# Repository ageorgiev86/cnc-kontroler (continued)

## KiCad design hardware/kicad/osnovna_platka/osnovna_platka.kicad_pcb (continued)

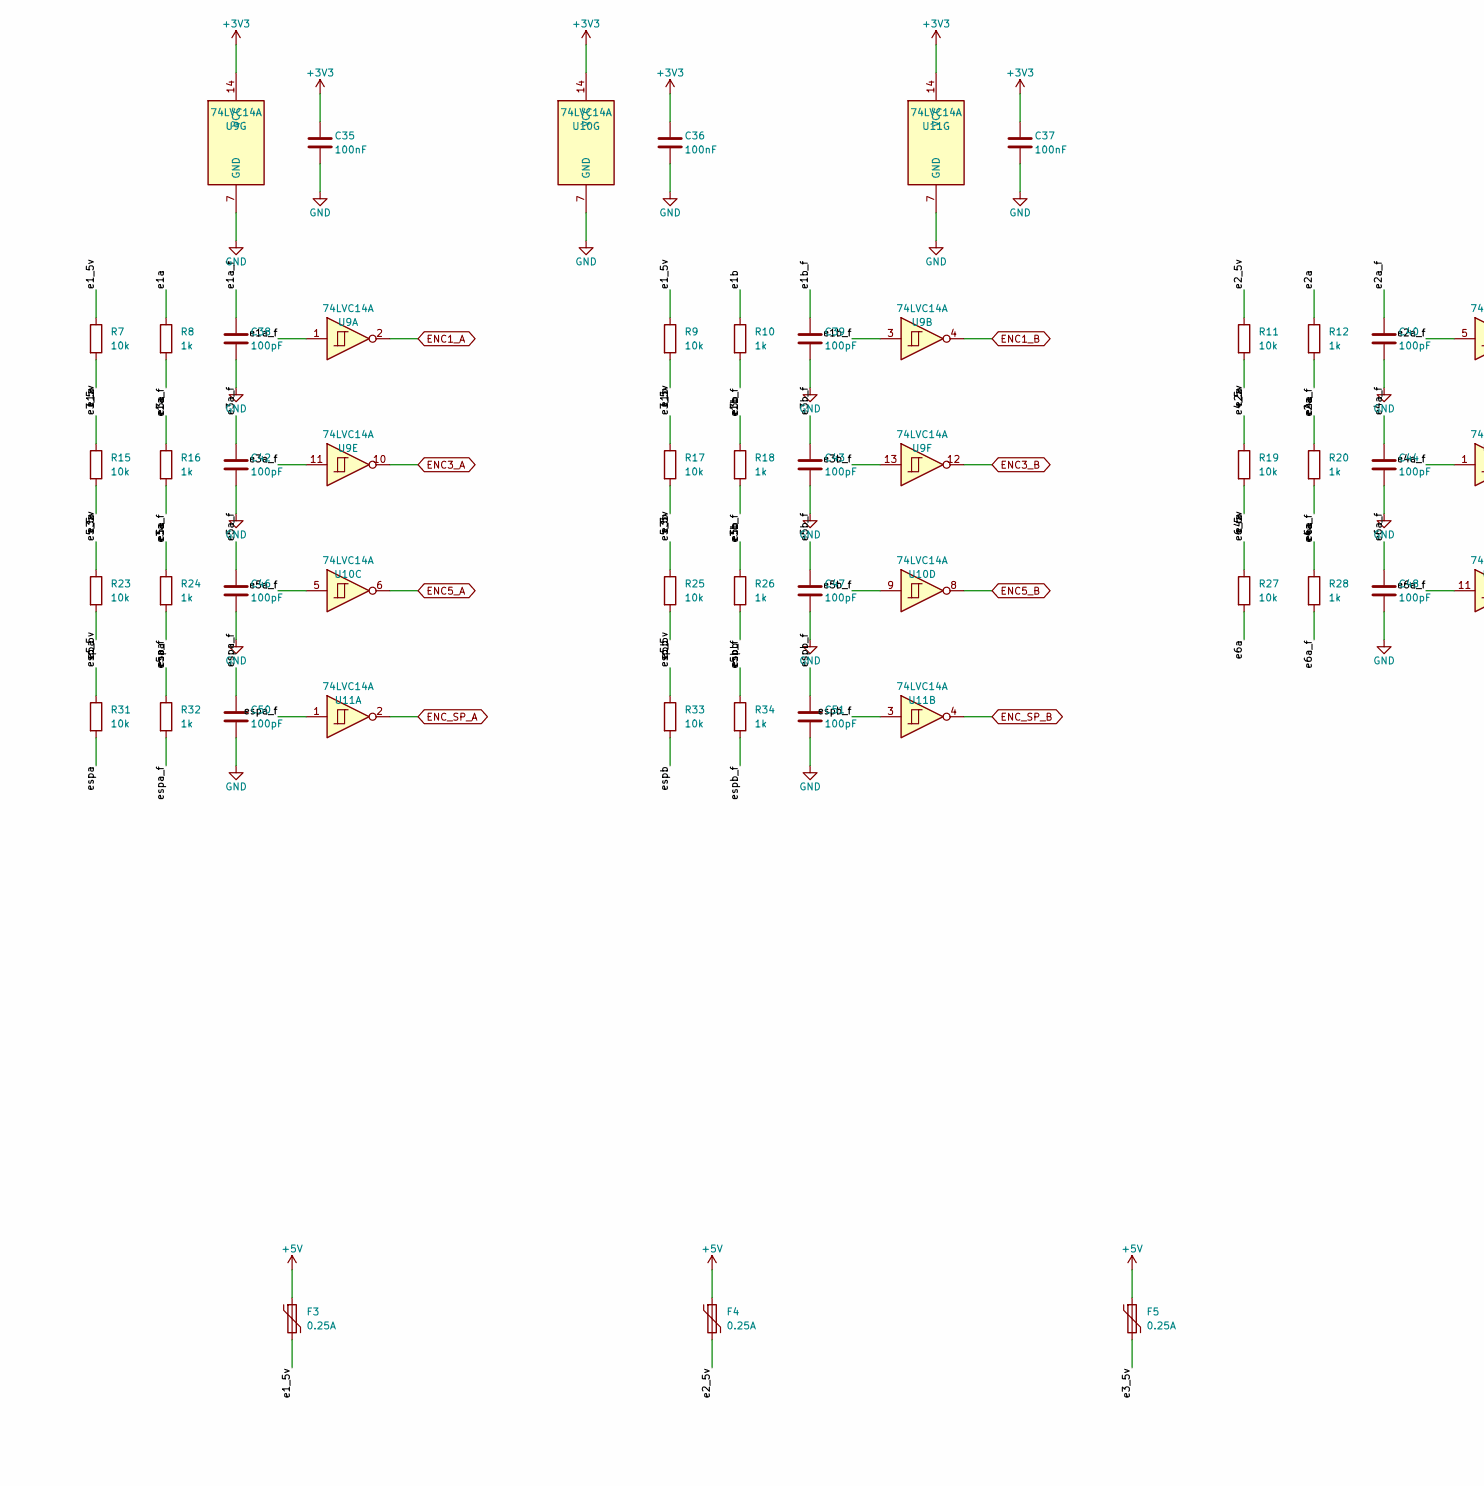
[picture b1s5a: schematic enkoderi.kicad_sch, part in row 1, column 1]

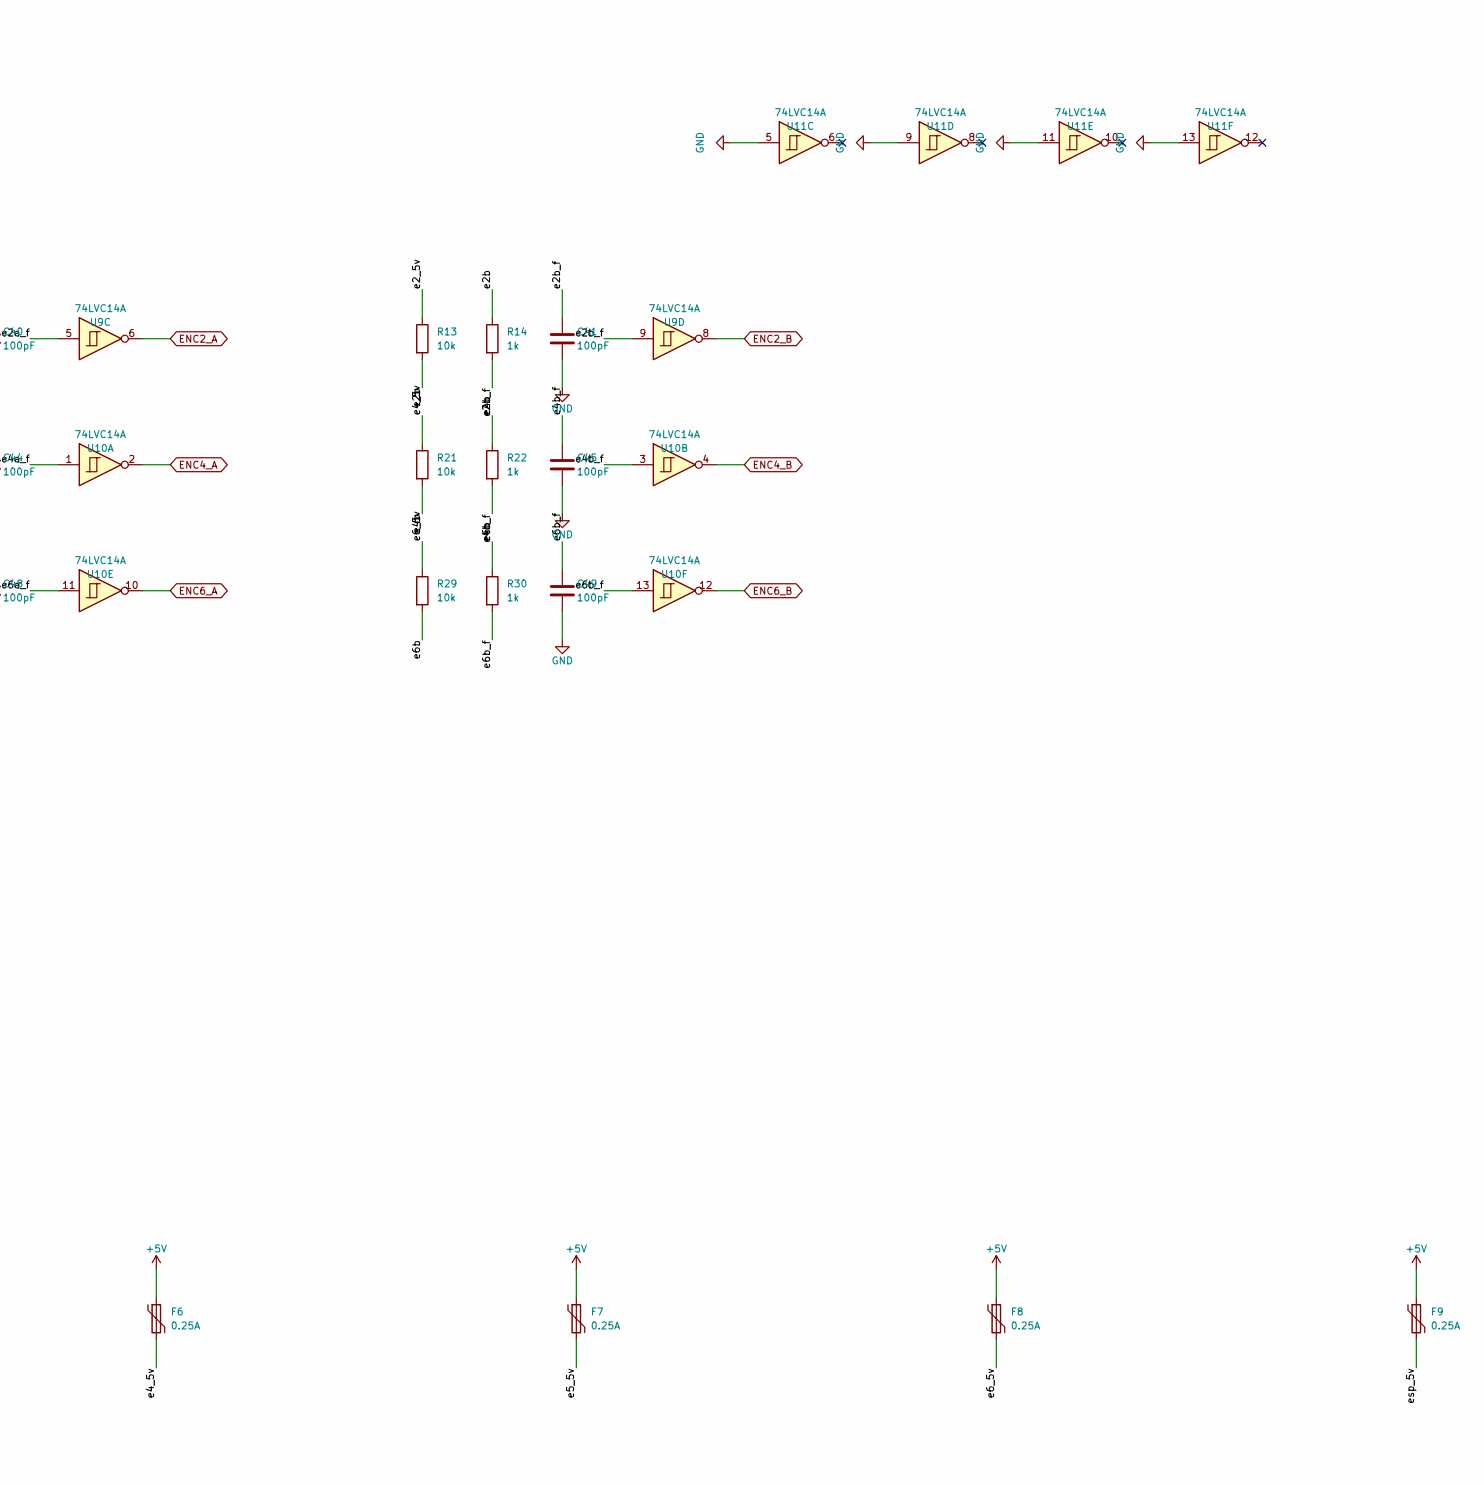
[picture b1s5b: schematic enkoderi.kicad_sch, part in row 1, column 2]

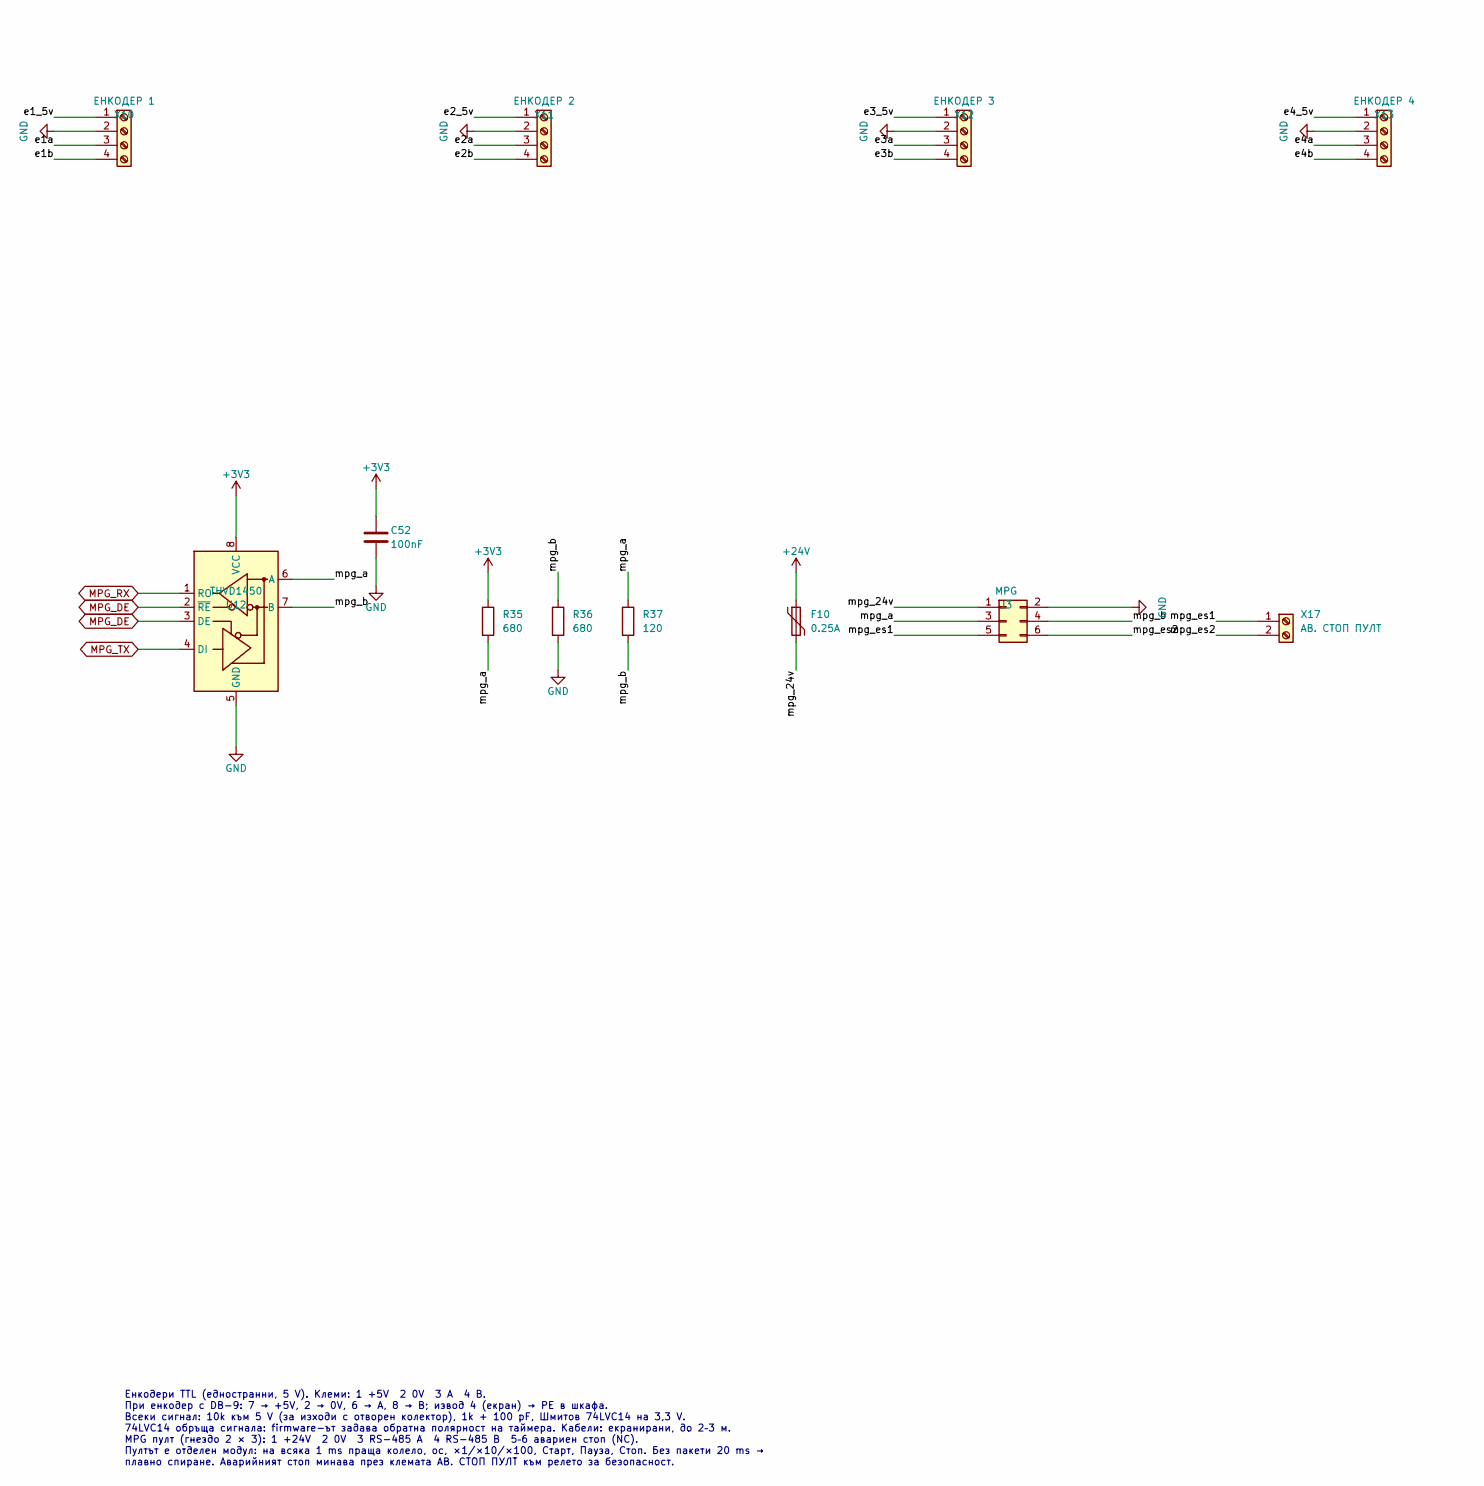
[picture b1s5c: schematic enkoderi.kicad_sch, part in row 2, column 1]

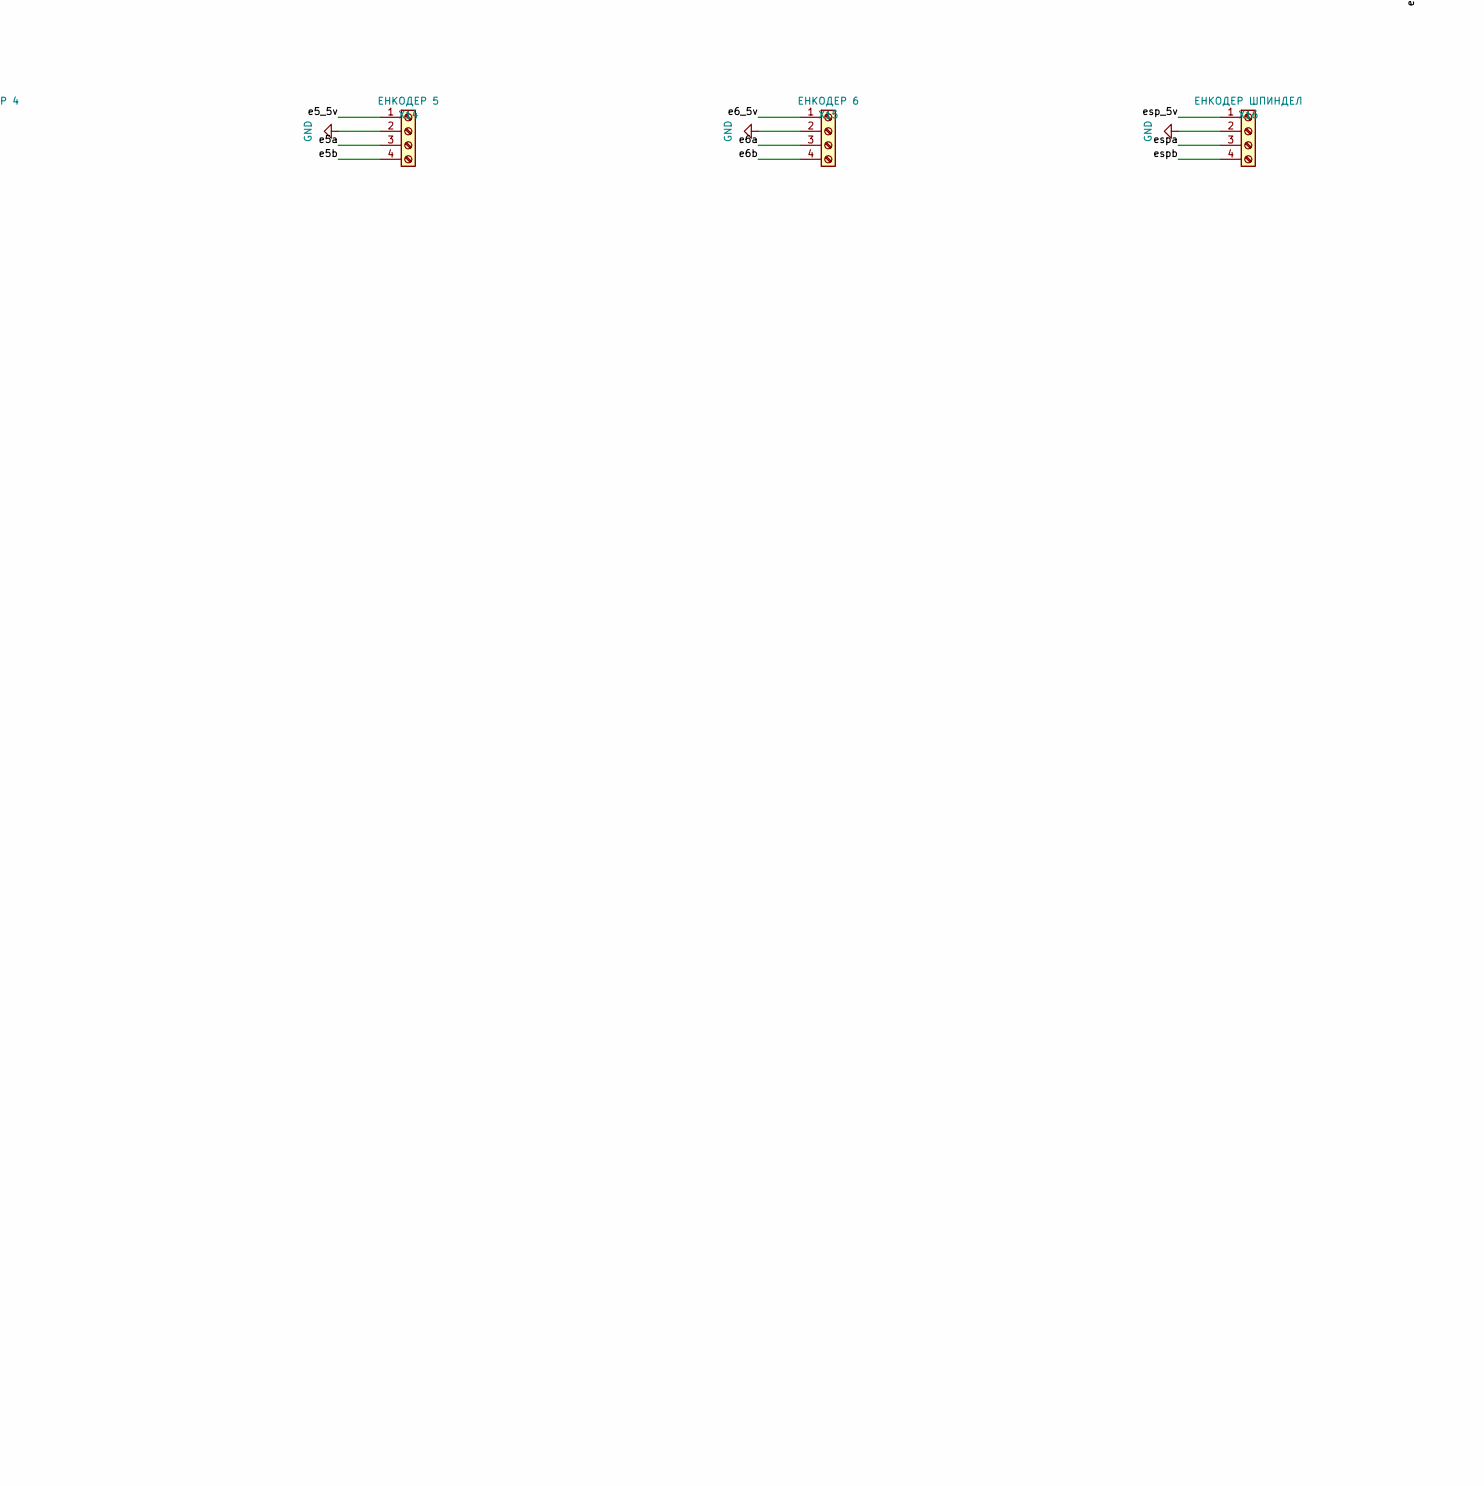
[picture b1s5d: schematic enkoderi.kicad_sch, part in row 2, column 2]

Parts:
C35, C36, C37, C52: 100nF; C_0805_2012Metric
C38, C39, C40, C41, C42, C43, C44, C45, C46, C47, C48, C49, C50, C51: 100pF; C_0805_2012Metric
F3, F4, F5, F6, F7, F8, F9, F10: 0.25A; Fuse_1206_3216Metric
J3: MPG; IDC-Header_2x03_P2.54mm_Vertical
R7, R9, R11, R13, R15, R17, R19, R21, R23, R25, R27, R29, R31, R33: 10k; R_0805_2012Metric
R8, R10, R12, R14, R16, R18, R20, R22, R24, R26, R28, R30, R32, R34: 1k; R_0805_2012Metric
R35, R36: 680; R_0805_2012Metric
R37: 120; R_0805_2012Metric
U9, U10, U11: 74LVC14A; SOIC-14_3.9x8.7mm_P1.27mm
U12: THVD1450; SOIC-8_3.9x4.9mm_P1.27mm
X10: ЕНКОДЕР 1; PhoenixContact_MSTBA_2,5_4-G-5,08_1x04_P5.08mm_Horizontal
X11: ЕНКОДЕР 2; PhoenixContact_MSTBA_2,5_4-G-5,08_1x04_P5.08mm_Horizontal
X12: ЕНКОДЕР 3; PhoenixContact_MSTBA_2,5_4-G-5,08_1x04_P5.08mm_Horizontal
X13: ЕНКОДЕР 4; PhoenixContact_MSTBA_2,5_4-G-5,08_1x04_P5.08mm_Horizontal
X14: ЕНКОДЕР 5; PhoenixContact_MSTBA_2,5_4-G-5,08_1x04_P5.08mm_Horizontal
X15: ЕНКОДЕР 6; PhoenixContact_MSTBA_2,5_4-G-5,08_1x04_P5.08mm_Horizontal
X16: ЕНКОДЕР ШПИНДЕЛ; PhoenixContact_MSTBA_2,5_4-G-5,08_1x04_P5.08mm_Horizontal
X17: АВ. СТОП ПУЛТ; PhoenixContact_MSTBA_2,5_2-G-5,08_1x02_P5.08mm_Horizontal

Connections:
+3V3: C35.1, C36.1, C37.1, C52.1, R35.1, U9.14 (VCC), U10.14 (VCC), U11.14 (VCC), U12.8 (VCC); also elsewhere on the board
+5V: F3.1, F4.1, F5.1, F6.1, F7.1, F8.1, F9.1; also elsewhere on the board
+24V: F10.1; also elsewhere on the board
/Енкодери и MPG/e1_5v: F3.2, R7.1, R9.1, X10.1
/Енкодери и MPG/e1a: R7.2, R8.1, X10.3
/Енкодери и MPG/e1a_f: C38.1, R8.2, U9.1
/Енкодери и MPG/e1b: R9.2, R10.1, X10.4
/Енкодери и MPG/e1b_f: C39.1, R10.2, U9.3
/Енкодери и MPG/e2_5v: F4.2, R11.1, R13.1, X11.1
/Енкодери и MPG/e2a: R11.2, R12.1, X11.3
/Енкодери и MPG/e2a_f: C40.1, R12.2, U9.5
/Енкодери и MPG/e2b: R13.2, R14.1, X11.4
/Енкодери и MPG/e2b_f: C41.1, R14.2, U9.9
/Енкодери и MPG/e3_5v: F5.2, R15.1, R17.1, X12.1
/Енкодери и MPG/e3a: R15.2, R16.1, X12.3
/Енкодери и MPG/e3a_f: C42.1, R16.2, U9.11
/Енкодери и MPG/e3b: R17.2, R18.1, X12.4
/Енкодери и MPG/e3b_f: C43.1, R18.2, U9.13
/Енкодери и MPG/e4_5v: F6.2, R19.1, R21.1, X13.1
/Енкодери и MPG/e4a: R19.2, R20.1, X13.3
/Енкодери и MPG/e4a_f: C44.1, R20.2, U10.1
/Енкодери и MPG/e4b: R21.2, R22.1, X13.4
/Енкодери и MPG/e4b_f: C45.1, R22.2, U10.3
/Енкодери и MPG/e5_5v: F7.2, R23.1, R25.1, X14.1
/Енкодери и MPG/e5a: R23.2, R24.1, X14.3
/Енкодери и MPG/e5a_f: C46.1, R24.2, U10.5
/Енкодери и MPG/e5b: R25.2, R26.1, X14.4
/Енкодери и MPG/e5b_f: C47.1, R26.2, U10.9
/Енкодери и MPG/e6_5v: F8.2, R27.1, R29.1, X15.1
/Енкодери и MPG/e6a: R27.2, R28.1, X15.3
/Енкодери и MPG/e6a_f: C48.1, R28.2, U10.11
/Енкодери и MPG/e6b: R29.2, R30.1, X15.4
/Енкодери и MPG/e6b_f: C49.1, R30.2, U10.13
/Енкодери и MPG/esp_5v: F9.2, R31.1, R33.1, X16.1
/Енкодери и MPG/espa: R31.2, R32.1, X16.3
/Енкодери и MPG/espa_f: C50.1, R32.2, U11.1
/Енкодери и MPG/espb: R33.2, R34.1, X16.4
/Енкодери и MPG/espb_f: C51.1, R34.2, U11.3
/Енкодери и MPG/mpg_24v: F10.2, J3.1
/Енкодери и MPG/mpg_a: J3.3, R35.2, R37.1, U12.6 (A)
/Енкодери и MPG/mpg_b: J3.4, R36.1, R37.2, U12.7 (B)
/Енкодери и MPG/mpg_es1: J3.5, X17.1
/Енкодери и MPG/mpg_es2: J3.6, X17.2
ENC1_A: U9.2; also elsewhere on the board
ENC1_B: U9.4; also elsewhere on the board
ENC2_A: U9.6; also elsewhere on the board
ENC2_B: U9.8; also elsewhere on the board
ENC3_A: U9.10; also elsewhere on the board
ENC3_B: U9.12; also elsewhere on the board
ENC4_A: U10.2; also elsewhere on the board
ENC4_B: U10.4; also elsewhere on the board
ENC5_A: U10.6; also elsewhere on the board
ENC5_B: U10.8; also elsewhere on the board
ENC6_A: U10.10; also elsewhere on the board
ENC6_B: U10.12; also elsewhere on the board
ENC_SP_A: U11.2; also elsewhere on the board
ENC_SP_B: U11.4; also elsewhere on the board
GND: C35.2, C36.2, C37.2, C38.2, C39.2, C40.2, C41.2, C42.2, C43.2, C44.2, C45.2, C46.2, C47.2, C48.2, C49.2, C50.2, C51.2, C52.2, J3.2, R36.2, U9.7 (GND), U10.7 (GND), U11.5, U11.7 (GND), U11.9, U11.11, U11.13, U12.5 (GND), X10.2, X11.2, X12.2, X13.2, X14.2, X15.2, X16.2; also elsewhere on the board
MPG_DE: U12.2 (~RE), U12.3 (DE); also elsewhere on the board
MPG_RX: U12.1 (RO); also elsewhere on the board
MPG_TX: U12.4 (DI); also elsewhere on the board

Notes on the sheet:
Енкодери TTL (едностранни, 5 V). Клеми: 1 +5V 2 0V 3 A 4 B. При енкодер с DB-9: 7 → +5V, 2 → 0V, 6 → A, 8 → B; извод 4 (екран) → PE в шкафа. Всеки сигнал: 10k към 5 V (за изходи с отворен колектор), 1k + 100 pF, Шмитов 74LVC14 на 3,3 V. 74LVC14 обръща сигнала: firmware-ът задава обратна полярност н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

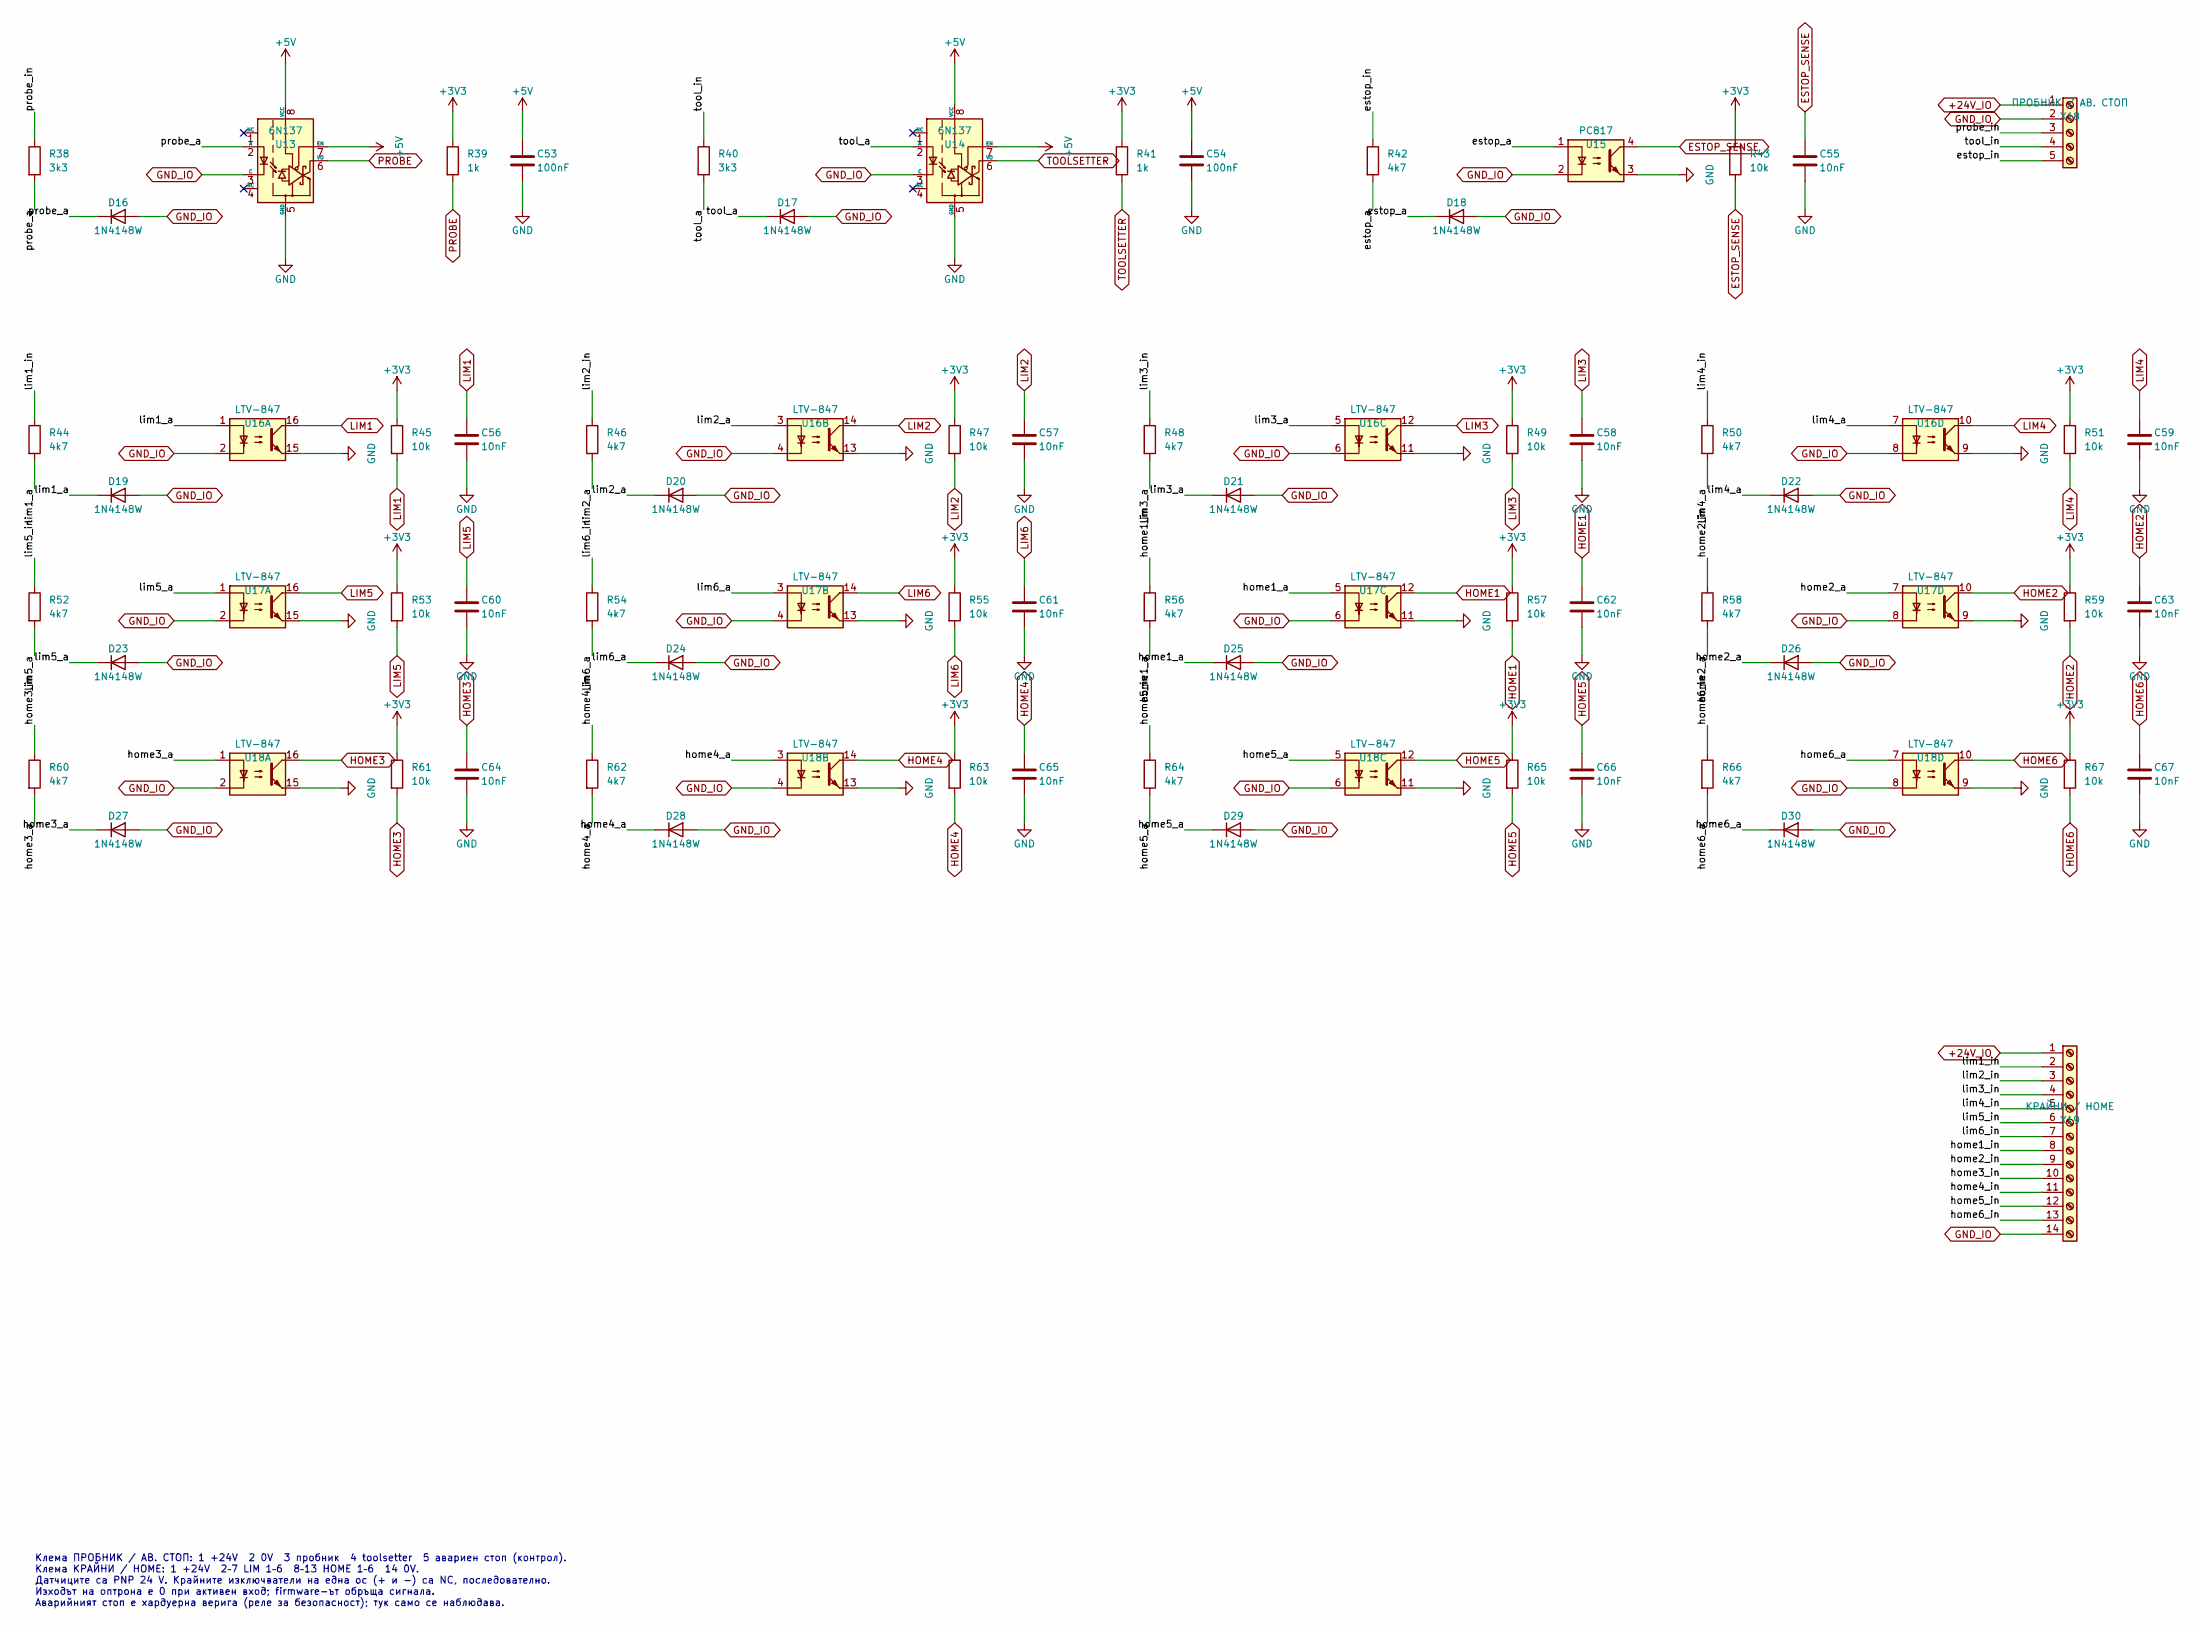
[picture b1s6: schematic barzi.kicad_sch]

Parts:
C53, C54: 100nF; C_0805_2012Metric
C55, C56, C57, C58, C59, C60, C61, C62, C63, C64, C65, C66, C67: 10nF; C_0805_2012Metric
D16, D17, D18, D19, D20, D21, D22, D23, D24, D25, D26, D27, D28, D29, D30: 1N4148W; D_SOD-323
R38, R40: 3k3; R_1206_3216Metric
R39, R41: 1k; R_0805_2012Metric
R42, R44, R46, R48, R50, R52, R54, R56, R58, R60, R62, R64, R66: 4k7; R_1206_3216Metric
R43, R45, R47, R49, R51, R53, R55, R57, R59, R61, R63, R65, R67: 10k; R_0805_2012Metric
U13, U14: 6N137; SMDIP-8_W7.62mm
U15: PC817; SMDIP-4_W7.62mm
U16, U17, U18: LTV-847; SMDIP-16_W7.62mm
X18: ПРОБНИК / АВ. СТОП; PhoenixContact_MSTBA_2,5_5-G-5,08_1x05_P5.08mm_Horizontal
X19: КРАЙНИ / HOME; PhoenixContact_MSTBA_2,5_14-G-5,08_1x14_P5.08mm_Horizontal

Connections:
+3V3: R39.1, R41.1, R43.1, R45.1, R47.1, R49.1, R51.1, R53.1, R55.1, R57.1, R59.1, R61.1, R63.1, R65.1, R67.1; also elsewhere on the board
+5V: C53.1, C54.1, U13.7 (EN), U13.8 (VCC), U14.7 (EN), U14.8 (VCC); also elsewhere on the board
+24V_IO: X18.1, X19.1; also elsewhere on the board
/Пробник, крайни, авариен стоп/estop_a: D18.1 (K), R42.2, U15.1
/Пробник, крайни, авариен стоп/estop_in: R42.1, X18.5
/Пробник, крайни, авариен стоп/home1_a: D25.1 (K), R56.2, U17.5
/Пробник, крайни, авариен стоп/home1_in: R56.1, X19.8
/Пробник, крайни, авариен стоп/home2_a: D26.1 (K), R58.2, U17.7
/Пробник, крайни, авариен стоп/home2_in: R58.1, X19.9
/Пробник, крайни, авариен стоп/home3_a: D27.1 (K), R60.2, U18.1
/Пробник, крайни, авариен стоп/home3_in: R60.1, X19.10
/Пробник, крайни, авариен стоп/home4_a: D28.1 (K), R62.2, U18.3
/Пробник, крайни, авариен стоп/home4_in: R62.1, X19.11
/Пробник, крайни, авариен стоп/home5_a: D29.1 (K), R64.2, U18.5
/Пробник, крайни, авариен стоп/home5_in: R64.1, X19.12
/Пробник, крайни, авариен стоп/home6_a: D30.1 (K), R66.2, U18.7
/Пробник, крайни, авариен стоп/home6_in: R66.1, X19.13
/Пробник, крайни, авариен стоп/lim1_a: D19.1 (K), R44.2, U16.1
/Пробник, крайни, авариен стоп/lim1_in: R44.1, X19.2
/Пробник, крайни, авариен стоп/lim2_a: D20.1 (K), R46.2, U16.3
/Пробник, крайни, авариен стоп/lim2_in: R46.1, X19.3
/Пробник, крайни, авариен стоп/lim3_a: D21.1 (K), R48.2, U16.5
/Пробник, крайни, авариен стоп/lim3_in: R48.1, X19.4
/Пробник, крайни, авариен стоп/lim4_a: D22.1 (K), R50.2, U16.7
/Пробник, крайни, авариен стоп/lim4_in: R50.1, X19.5
/Пробник, крайни, авариен стоп/lim5_a: D23.1 (K), R52.2, U17.1
/Пробник, крайни, авариен стоп/lim5_in: R52.1, X19.6
/Пробник, крайни, авариен стоп/lim6_a: D24.1 (K), R54.2, U17.3
/Пробник, крайни, авариен стоп/lim6_in: R54.1, X19.7
/Пробник, крайни, авариен стоп/probe_a: D16.1 (K), R38.2, U13.2 (A)
/Пробник, крайни, авариен стоп/probe_in: R38.1, X18.3
/Пробник, крайни, авариен стоп/tool_a: D17.1 (K), R40.2, U14.2 (A)
/Пробник, крайни, авариен стоп/tool_in: R40.1, X18.4
ESTOP_SENSE: C55.1, R43.2, U15.4; also elsewhere on the board
GND: C53.2, C54.2, C55.2, C56.2, C57.2, C58.2, C59.2, C60.2, C61.2, C62.2, C63.2, C64.2, C65.2, C66.2, C67.2, U13.5 (GND), U14.5 (GND), U15.3, U16.9, U16.11, U16.13, U16.15, U17.9, U17.11, U17.13, U17.15, U18.9, U18.11, U18.13, U18.15; also elsewhere on the board
GND_IO: D16.2 (A), D17.2 (A), D18.2 (A), D19.2 (A), D20.2 (A), D21.2 (A), D22.2 (A), D23.2 (A), D24.2 (A), D25.2 (A), D26.2 (A), D27.2 (A), D28.2 (A), D29.2 (A), D30.2 (A), U13.3 (C), U14.3 (C), U15.2, U16.2, U16.4, U16.6, U16.8, U17.2, U17.4, U17.6, U17.8, U18.2, U18.4, U18.6, U18.8, X18.2, X19.14; also elsewhere on the board
HOME1: C62.1, R57.2, U17.12; also elsewhere on the board
HOME2: C63.1, R59.2, U17.10; also elsewhere on the board
HOME3: C64.1, R61.2, U18.16; also elsewhere on the board
HOME4: C65.1, R63.2, U18.14; also elsewhere on the board
HOME5: C66.1, R65.2, U18.12; also elsewhere on the board
HOME6: C67.1, R67.2, U18.10; also elsewhere on the board
LIM1: C56.1, R45.2, U16.16; also elsewhere on the board
LIM2: C57.1, R47.2, U16.14; also elsewhere on the board
LIM3: C58.1, R49.2, U16.12; also elsewhere on the board
LIM4: C59.1, R51.2, U16.10; also elsewhere on the board
LIM5: C60.1, R53.2, U17.16; also elsewhere on the board
LIM6: C61.1, R55.2, U17.14; also elsewhere on the board
PROBE: R39.2, U13.6 (VO); also elsewhere on the board
TOOLSETTER: R41.2, U14.6 (VO); also elsewhere on the board

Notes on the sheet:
Клема ПРОБНИК / АВ. СТОП: 1 +24V 2 0V 3 пробник 4 toolsetter 5 авариен стоп (контрол). Клема КРАЙНИ / HOME: 1 +24V 2–7 LIM 1–6 8–13 HOME 1–6 14 0V. Датчиците са PNP 24 V. Крайните изключватели на една ос (+ и −) са NC, последователно. Изходът на оптрона е 0 при активен вход; firmware-ът обръща сигн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
